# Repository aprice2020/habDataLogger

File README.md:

# habDataLogger
High Altitude Balloon Data Logger -
GPS based data logger for high altitude balloon use.
Can be used with CO2 sensor, geiger counter, etc.
Stores logs on microSD card.

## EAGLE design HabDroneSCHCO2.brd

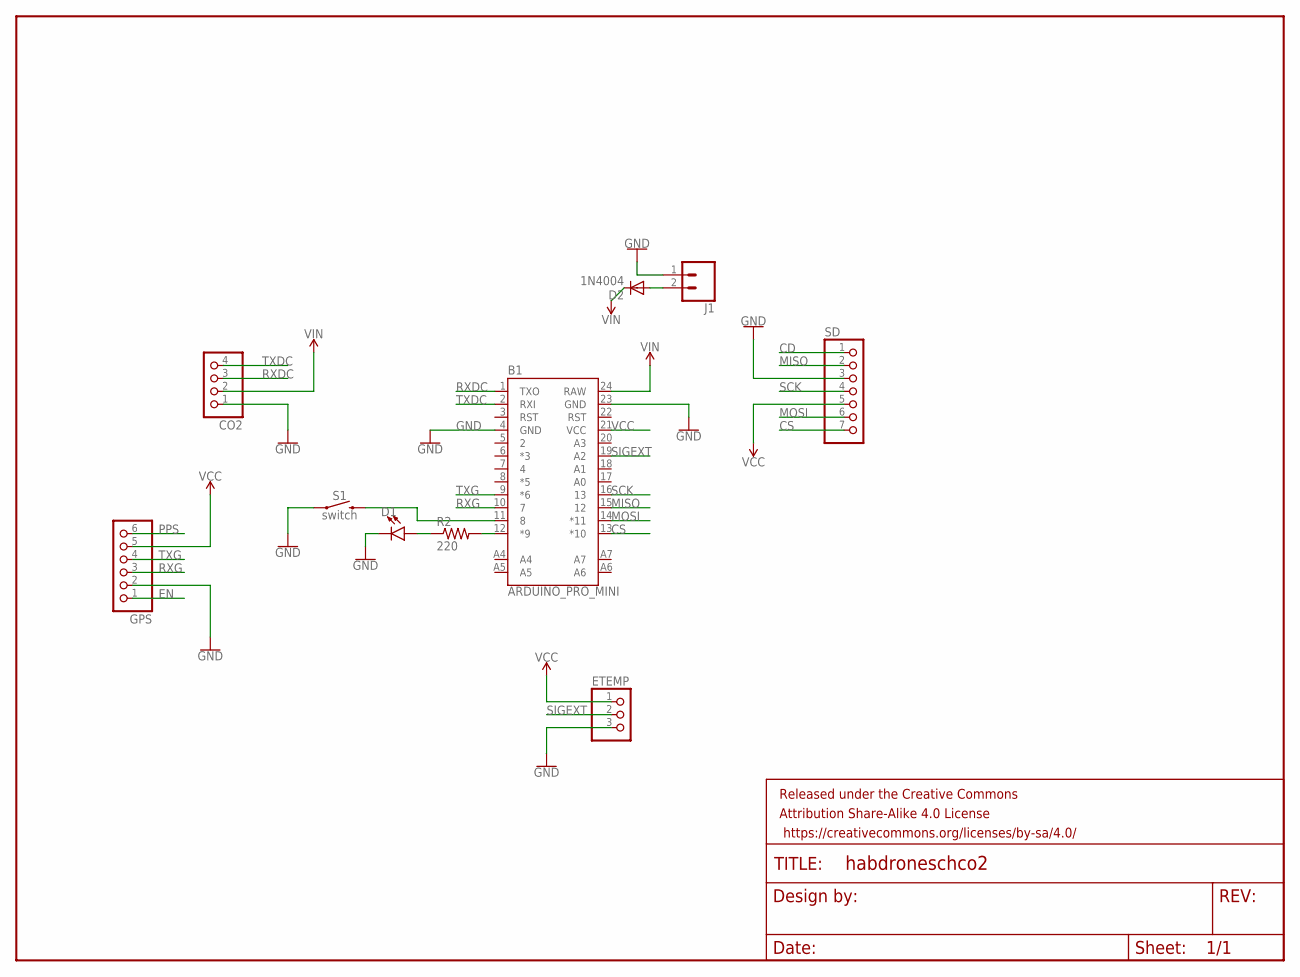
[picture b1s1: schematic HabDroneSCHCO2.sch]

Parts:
B1: ARDUINO_PRO_MINI
CO2: PINHD-1X4/90; 1X04/90
D1: LED5MM; LED_5MM
D2: 1N4004; DO41-10
ETEMP: PINHD-1X3/90; 1X03/90
FRAME1: FRAME-LETTERNO_PACKAGE; DUMMY
GPS: PINHD-1X6/90; 1X06/90
J1: CONN_025MM; SCREWTERMINAL-5MM-2
R2: 220; VMTA55
S1: switch; TACTILE_SWITCH_PTH_6.0MM
SD: PINHD-1X7/90; 1X07/90

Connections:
CD: SD.1
CS: B1.13 (*10), SD.7
EN: GPS.1
GND: B1.4 (GND), B1.23 (GND), CO2.1, D1.K (C), ETEMP.3, GPS.2, J1.1, S1.1, SD.3
MISO: B1.15 (12), SD.2
MOSI: B1.14 (*11), SD.6
unnamed: D2.A, J1.2
unnamed: B1.11 (8), S1.3 (2)
unnamed: B1.12 (*9), R2.2
unnamed: D1.A, R2.1
PPS: GPS.6
RXDC: B1.1 (TXO), CO2.3
RXG: B1.10 (7), GPS.3
SCK: B1.16 (13), SD.4
SIGEXT: B1.19 (A2), ETEMP.2
TXDC: B1.2 (RXI), CO2.4
TXG: B1.9 (*6), GPS.4
VCC: B1.21 (VCC), ETEMP.1, GPS.5, SD.5
VIN: B1.24 (RAW), CO2.2, D2.C

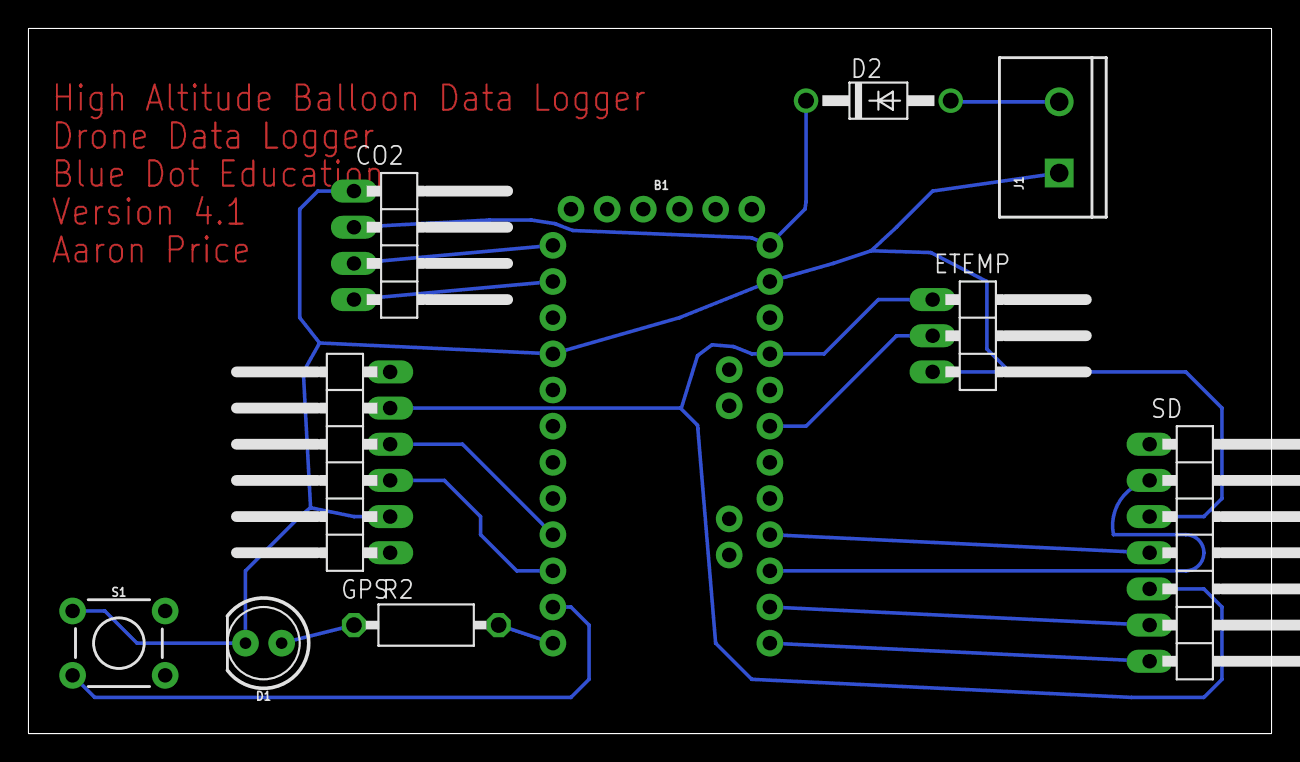
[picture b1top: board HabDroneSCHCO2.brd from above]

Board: 2 copper layers, 87.3 x 49.5 mm, 11 parts (0 on the bottom side), 16 nets.

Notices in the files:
parts and their libraries:
SparkFun-Boards: Licensing: Creative Commons ShareAlike 4.0 International - https://creativecommons.org/licenses/by-sa/4.0
SparkFun-Aesthetics: Released under the Creative Commons Attribution Share-Alike 4.0 License
SparkFun-Aesthetics: https://creativecommons.org/licenses/by-sa/4.0
